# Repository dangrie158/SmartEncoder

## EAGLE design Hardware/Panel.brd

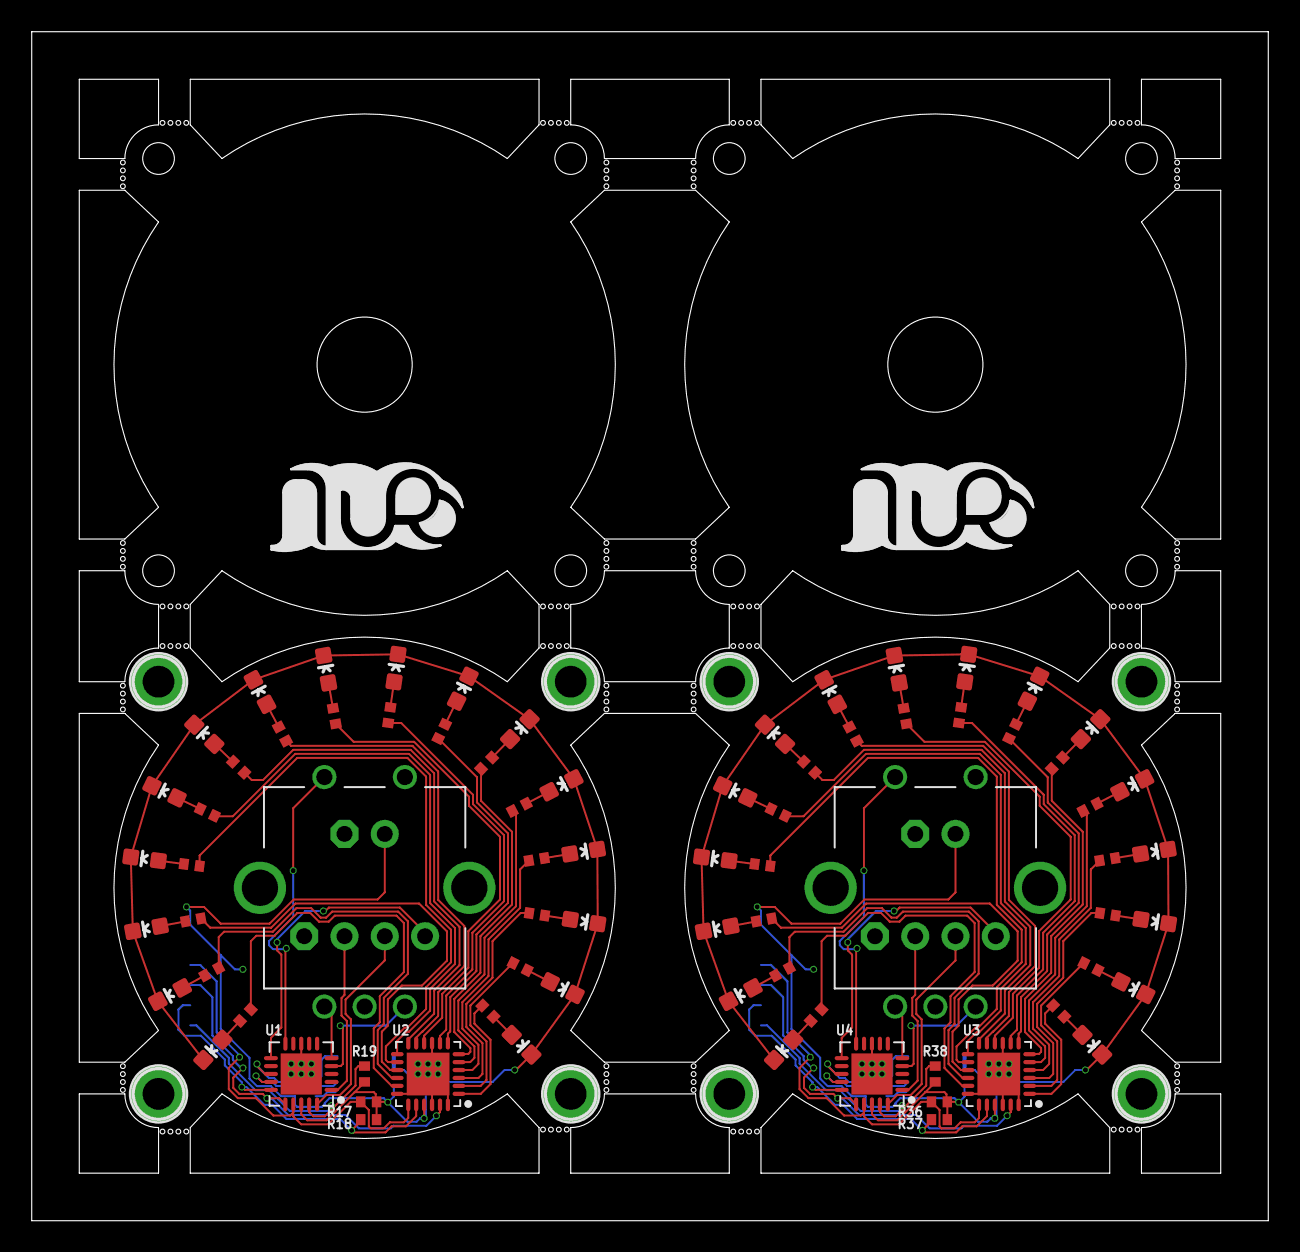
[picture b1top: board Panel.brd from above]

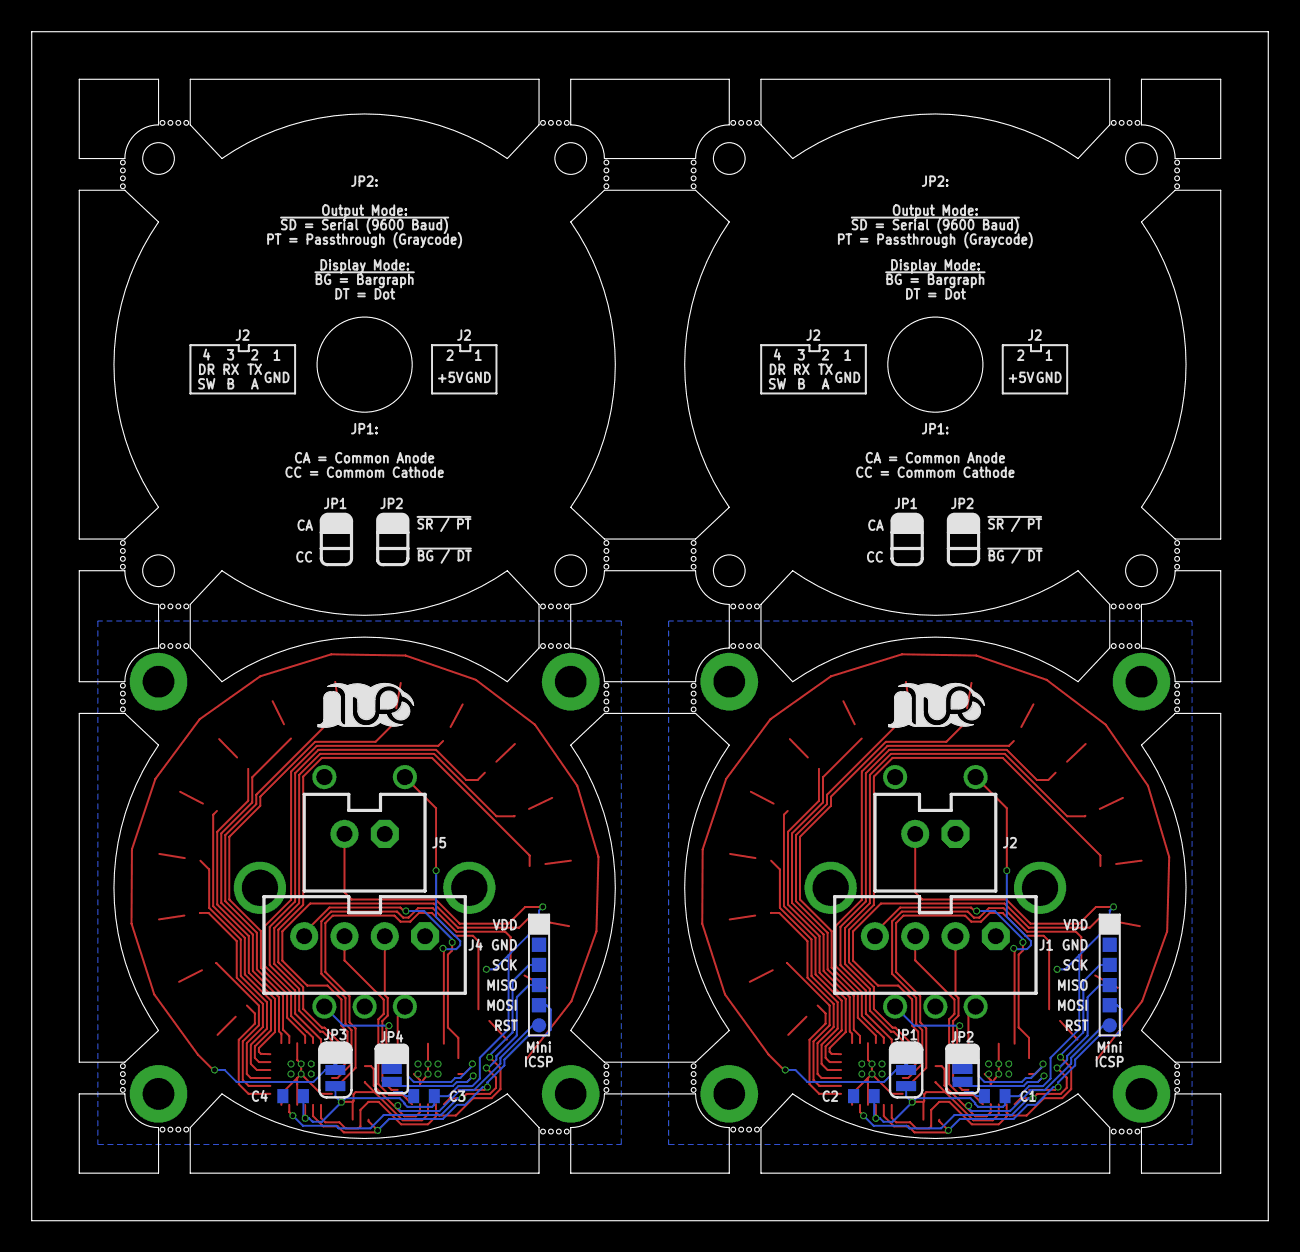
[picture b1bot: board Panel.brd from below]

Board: 2 copper layers, 78.0 x 75.0 mm, 102 parts (16 on the bottom side), 94 nets.

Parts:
C1, C2, C3, C4: 100n; C0402
H1, H2, H3, H4, H5, H6, H7, H8: 2mm; 2,0-PAD
J1, J4: OUT; JST-4-PTH-VERT
J2, J5: POWER; JST-2-PTH-VERT
J3, J6: ICSP; MINI-ISP-LABELS
JP1, JP3: JUMPER-SMT_3_1-NC_TRACE_SILK; SMT-JUMPER_3_1-NC_TRACE_SILK
JP2, JP4: MODE; SMT-JUMPER_3_NO_SILK
LED1, LED2, LED3, LED4, LED5, LED6, LED7, LED8, LED9, LED10, LED11, LED12, LED13, LED14, LED15, LED16, LED17, LED18, LED19, LED20, LED21, LED22, LED23, LED24, LED25, LED26, LED27, LED28, LED29, LED30, LED31, LED32: 0603-BLUE
R1, R2, R3, R4, R5, R6, R7, R8, R9, R10, R11, R12, R13, R14, R15, R16, R20, R21, R22, R23, R24, R25, R26, R27, R28, R29, R30, R31, R32, R33, R34, R35: 100; R0402
R17, R18, R19, R36, R37, R38: 4k7; R0402
SW1, SW2: ROTARY_ENC_PLAIN
U1, U4: ATTINY2313A; QFN50P400X400X80-21T260N
U2, U3: AW9523B; QFN50P400X400X80-25T270N
U$1, U$4: LOGO-SILKSCREEN
U$2, U$3: LOGO-SILKSCREEEN-S

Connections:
+5V: C1.1, C2.1, J2.2, J3.VDD, JP1.1, R17.2, R18.2, R19.2, U1.18, U2.21
+5V1: C3.1, C4.1, J5.2, J6.VDD, JP3.1, R36.2, R37.2, R38.2, U3.21, U4.18
GND: C1.2, C2.2, H1.B2,0, H2.B2,0, H3.B2,0, H4.B2,0, J1.1, J2.1, J3.GND, JP1.3, JP2.2, SW1.C, SW1.SW+, U1.8, U1.21, U2.9, U2.18, U2.22, U2.24, U2.25
GND1: C3.2, C4.2, H5.B2,0, H6.B2,0, H7.B2,0, H8.B2,0, J4.1, J5.1, J6.GND, JP3.3, JP4.2, SW2.C, SW2.SW+, U3.9, U3.18, U3.22, U3.24, U3.25, U4.8, U4.21
unnamed: J3.RESET, R19.1, U1.19
unnamed: LED12.A, R12.2
unnamed: LED11.A, R11.2
unnamed: LED10.A, R10.2
unnamed: LED9.A, R9.2
unnamed: LED8.A, R8.2
unnamed: LED7.A, R7.2
unnamed: LED6.A, R6.2
unnamed: LED5.A, R5.2
unnamed: LED16.A, R16.2
unnamed: LED15.A, R15.2
unnamed: LED14.A, R14.2
unnamed: LED13.A, R13.2
unnamed: LED4.A, R4.2
unnamed: LED3.A, R3.2
unnamed: LED2.A, R2.2
unnamed: LED1.A, R1.2
unnamed: J3.SCK, R17.1, U1.17, U2.19
unnamed: J3.MISO, U1.16, U2.23
unnamed: J1.3, U1.20
unnamed: R12.1, U2.5
unnamed: R11.1, U2.6
unnamed: R10.1, U2.7
unnamed: R9.1, U2.8
unnamed: R8.1, U2.10
unnamed: R7.1, U2.11
unnamed: R6.1, U2.12
unnamed: R5.1, U2.13
unnamed: R16.1, U2.1
unnamed: R15.1, U2.2
unnamed: R14.1, U2.3
unnamed: R13.1, U2.4
unnamed: R4.1, U2.14
unnamed: R3.1, U2.15
unnamed: R2.1, U2.16
unnamed: R1.1, U2.17
unnamed: SW1.A, U1.5
unnamed: SW1.SW-, U1.10
unnamed: J1.2, U1.1
unnamed: SW1.B, U1.4
unnamed: J3.MOSI, R18.1, U1.15, U2.20
unnamed: J1.4, U1.11
unnamed: JP2.3, U1.13
unnamed: JP2.1, U1.14
unnamed: JP1.2, LED1.C, LED2.C, LED3.C, LED4.C, LED5.C, LED6.C, LED7.C, LED8.C, LED9.C, LED10.C, LED11.C, LED12.C, LED13.C, LED14.C, LED15.C, LED16.C
unnamed: J6.SCK, R36.1, U3.19, U4.17
unnamed: SW2.B, U4.4
unnamed: LED20.A, R23.2
unnamed: LED19.A, R22.2
unnamed: LED18.A, R21.2
unnamed: LED32.A, R35.2
unnamed: LED31.A, R34.2
unnamed: LED30.A, R33.2
unnamed: LED29.A, R32.2
unnamed: LED28.A, R31.2
unnamed: LED24.A, R27.2
unnamed: LED23.A, R26.2
unnamed: LED22.A, R25.2
unnamed: LED21.A, R24.2
unnamed: LED27.A, R30.2
unnamed: LED26.A, R29.2
unnamed: LED25.A, R28.2
unnamed: LED17.A, R20.2
unnamed: R23.1, U3.5
unnamed: R22.1, U3.6
unnamed: R21.1, U3.7
unnamed: R35.1, U3.8
unnamed: R34.1, U3.10
unnamed: R32.1, U3.12
unnamed: R31.1, U3.13
unnamed: R27.1, U3.1
unnamed: R26.1, U3.2
unnamed: R25.1, U3.3
unnamed: R24.1, U3.4
unnamed: R30.1, U3.14
unnamed: R29.1, U3.15
unnamed: R33.1, U3.11
unnamed: R28.1, U3.16
unnamed: R20.1, U3.17
unnamed: J6.RESET, R38.1, U4.19
unnamed: J6.MOSI, R37.1, U3.20, U4.15
unnamed: J6.MISO, U3.23, U4.16
unnamed: SW2.SW-, U4.10
unnamed: J4.2, U4.1
unnamed: J4.4, U4.11
unnamed: JP4.3, U4.13
unnamed: JP4.1, U4.14
unnamed: SW2.A, U4.5
unnamed: J4.3, U4.20
unnamed: JP3.2, LED17.C, LED18.C, LED19.C, LED20.C, LED21.C, LED22.C, LED23.C, LED24.C, LED25.C, LED26.C, LED27.C, LED28.C, LED29.C, LED30.C, LED31.C, LED32.C

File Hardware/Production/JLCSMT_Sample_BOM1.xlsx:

Comment | Designator | Footprint | LCSC Part #（optional）
 | LED1, LED2, LED3, LED4, LED5, LED6, LED7, LED8, LED9, LED10, LED11, LED12, LED1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 | 0603 | C2290
100 | R1, R2, R3, R4, R5, R6, R7, R8, R9, R10, R11, R12, R13, R14, R15, R16 | R0402 | C25076
100n | C1, C2 | C0402 | C1525
4k7 | R17, R18, R19 | R0402 | C25900
ATTINY2313A | U1 | QFN50P400X400X80-21T260N | C185530
AW9523B | U2 | QFN50P400X400X80-25T270N | C148077

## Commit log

2019-11-01 initial commit for Hardware
2019-11-01 added first version of IO expander library
2019-11-03 updated board layout to optimize for DFM
2019-11-06 switched to avrlibc code, removed arduino deps
2019-11-06 updated hardware files with latest production run
2019-11-07 simplified makefile
2019-11-07 initialized static member in Wire Lib
2019-12-29 fixed bit flipped for io expander LED mode
2019-12-29 firmware functionality improvements
2019-12-29 implemented both display options
2019-12-29 added timer to servioce encoder
2019-12-29 changed pin definitions to mnemonic names
2019-12-29 added overflow handling
2019-12-29 added turn direction inversion
2019-12-29 added avr libc includepath to vs config
2019-12-29 added saving of settings
2019-12-29 changed signature of Serial::write
2019-12-29 removed unused initialization opf IO expander
2019-12-29 added definition for used MCU
2019-12-29 added Serial output and input options

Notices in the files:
parts and their libraries:
SparkFun-Jumpers: Licensing: Creative Commons ShareAlike 4.0 International - https://creativecommons.org/licenses/by-sa/4.0
